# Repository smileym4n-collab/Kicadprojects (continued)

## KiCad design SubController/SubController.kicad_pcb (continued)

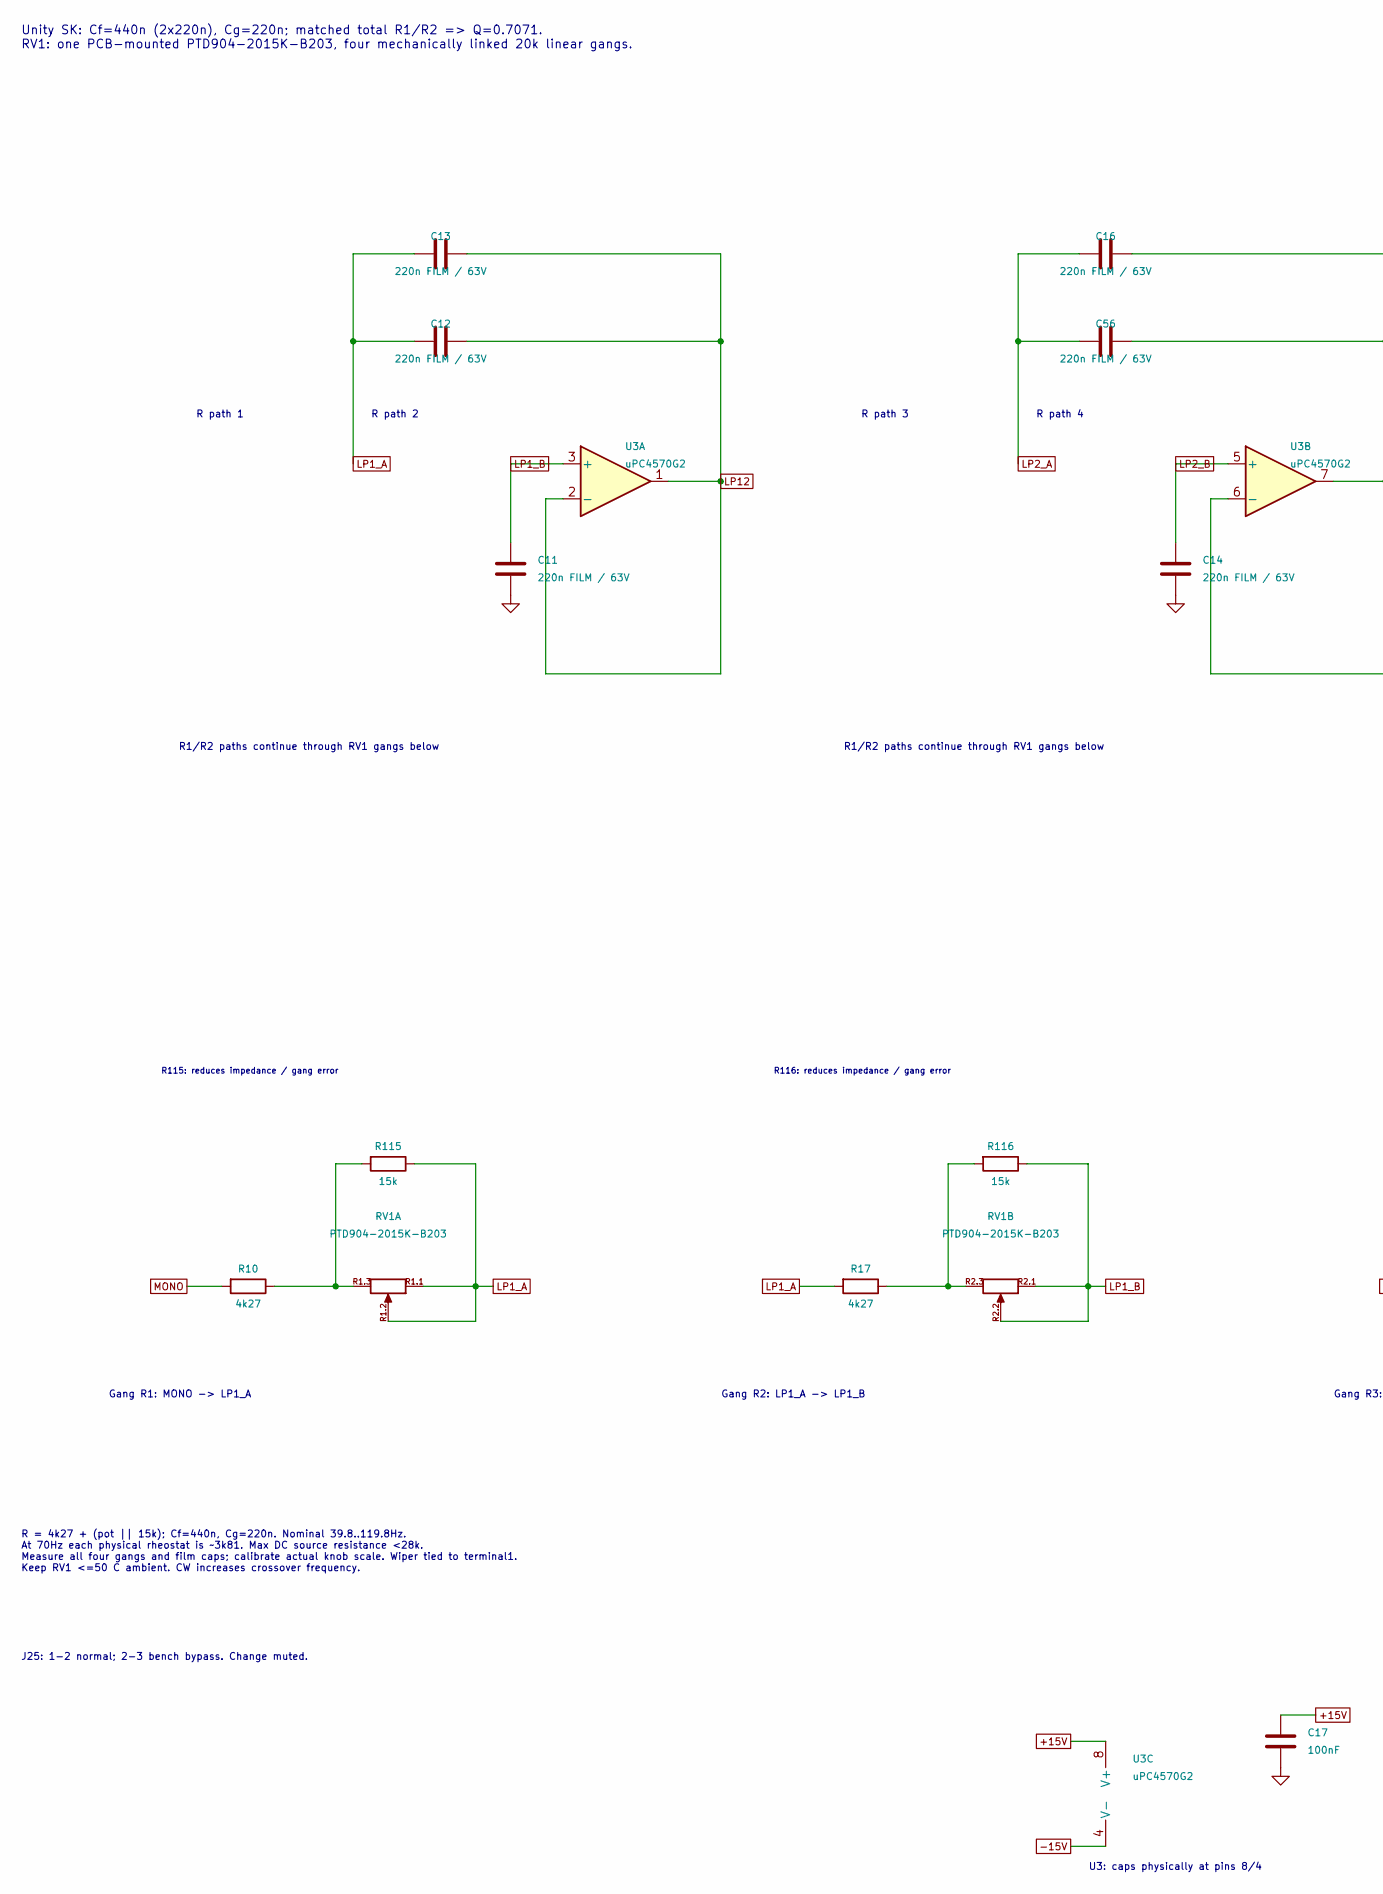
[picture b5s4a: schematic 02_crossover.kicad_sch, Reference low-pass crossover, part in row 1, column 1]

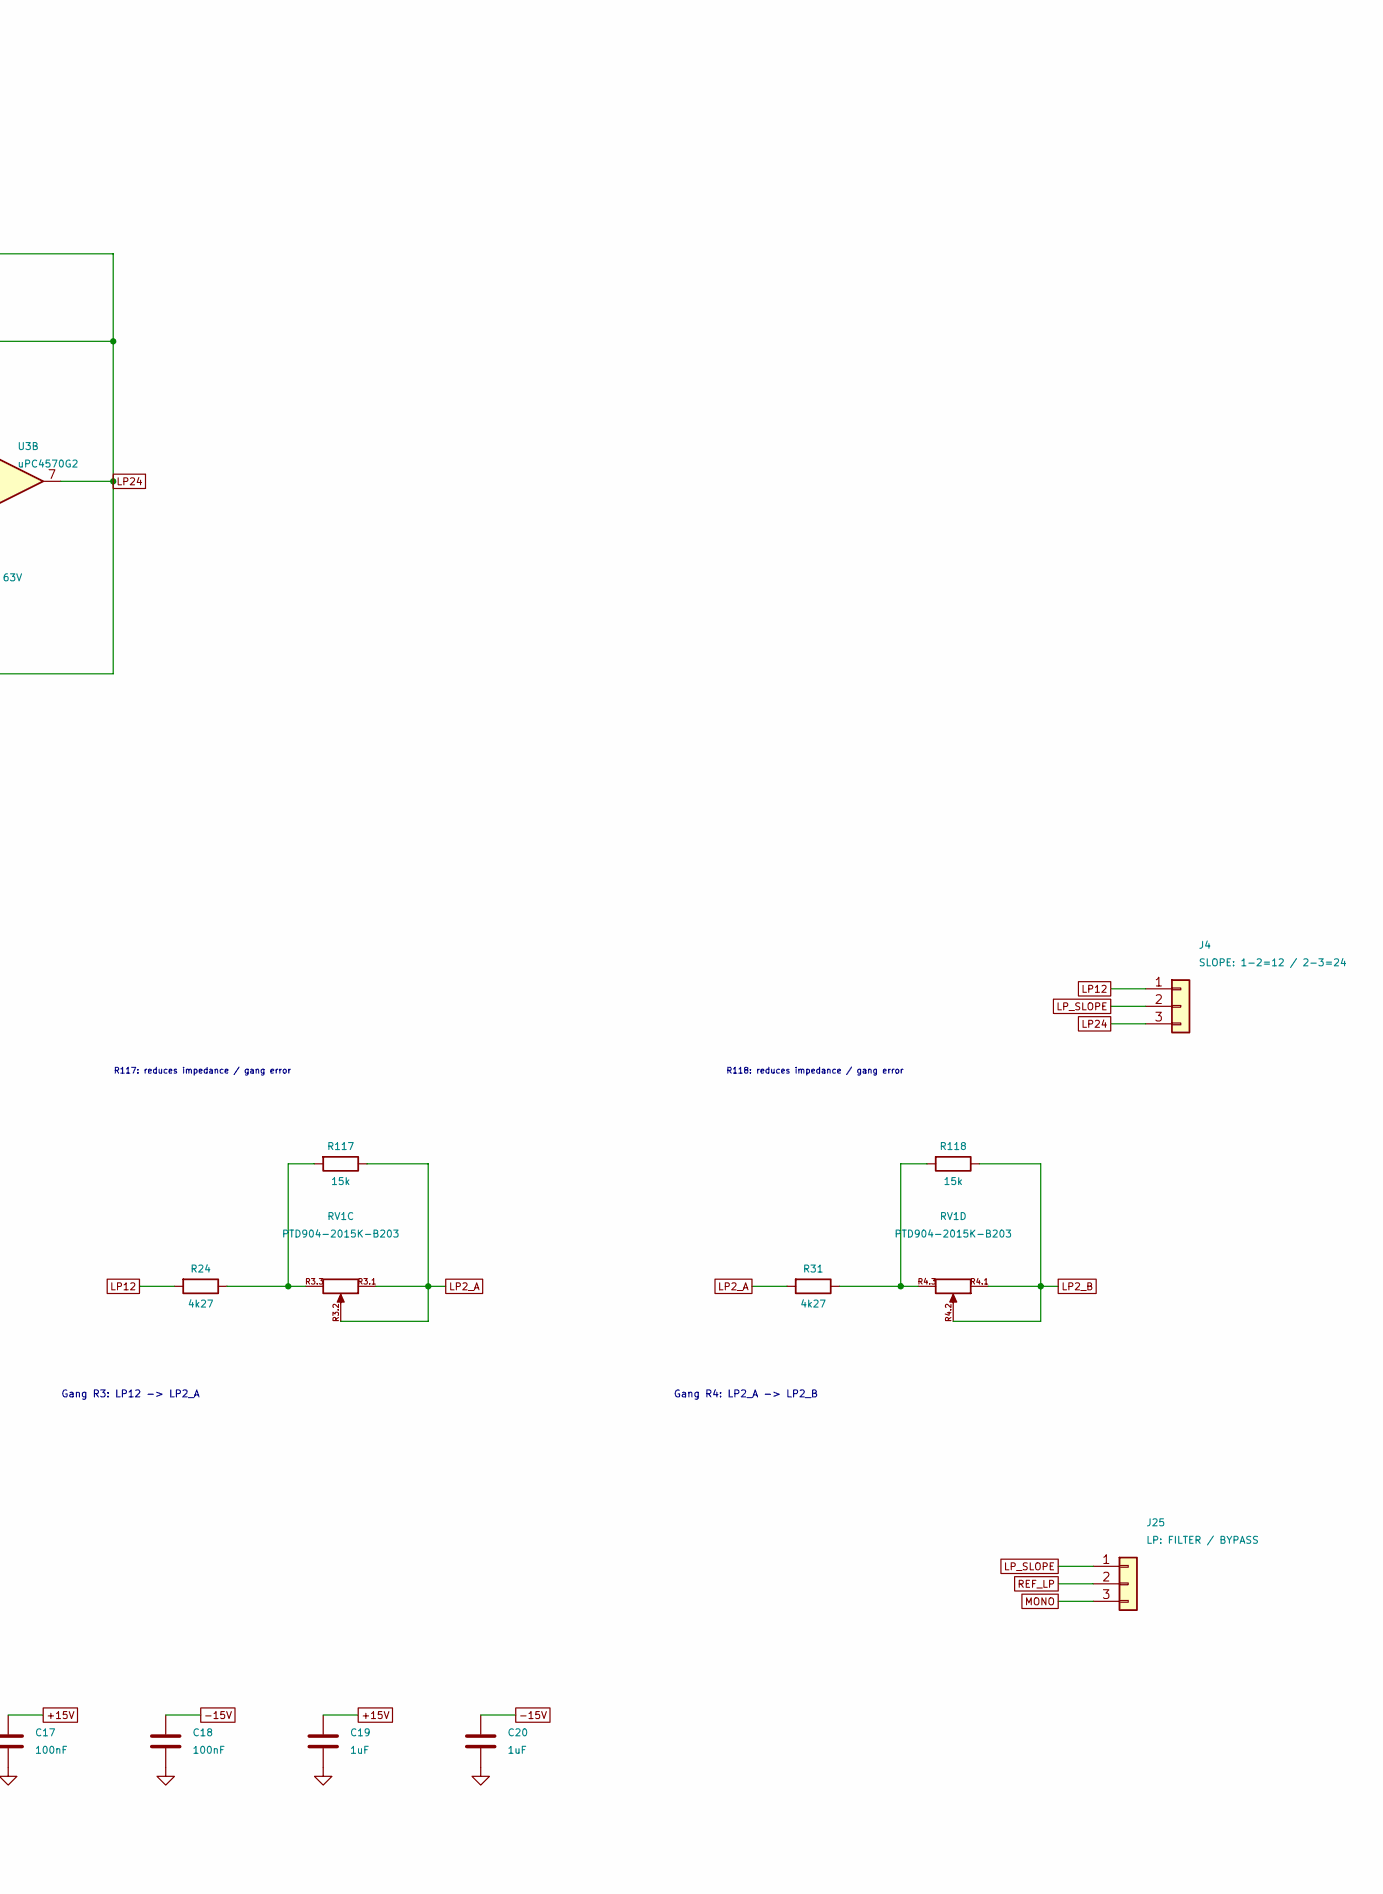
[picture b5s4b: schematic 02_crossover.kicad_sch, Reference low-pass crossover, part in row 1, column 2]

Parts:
C11, C12, C13, C14, C16, C56: 220n FILM / 63V; C_Rect_L7.2mm_W2.5mm_P5.00mm_FKS2_FKP2_MKS2_MKP2
C17, C18: 100nF; C_1206_3216Metric
C19, C20: 1uF; C_1206_3216Metric
J4: SLOPE: 1-2=12 / 2-3=24; PinHeader_1x03_P2.54mm_Vertical
J25: LP: FILTER / BYPASS; PinHeader_1x03_P2.54mm_Vertical
R10, R17, R24, R31: 4k27; R_0805_2012Metric
R115, R116, R117, R118: 15k; R_0805_2012Metric
RV1: PTD904-2015K-B203; PTD904_2015K_B203_Horizontal
U3: uPC4570G2; SOP-8_uPC4570G2_4.4x5.2mm_P1.27mm

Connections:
+15V: C17.1, C19.1, U3.8 (V+); also elsewhere on the board
-15V: C18.1, C20.1, U3.4 (V-); also elsewhere on the board
GND: C11.2, C14.2, C17.2, C18.2, C19.2, C20.2; also elsewhere on the board
LP1_A: C12.2, C13.2, R17.2, R115.1, RV1.R1.1 (1), RV1.R1.2 (2)
LP1_B: C11.1, R116.1, RV1.R2.1 (1), RV1.R2.2 (2), U3.3 (+)
LP2_A: C16.2, C56.2, R31.2, R117.1, RV1.R3.1 (1), RV1.R3.2 (2)
LP2_B: C14.1, R118.1, RV1.R4.1 (1), RV1.R4.2 (2), U3.5 (+)
LP12: C12.1, C13.1, J4.1, R24.2, U3.1, U3.2 (-)
LP24: C16.1, C56.1, J4.3, U3.6 (-), U3.7
LP_SLOPE: J4.2, J25.1; also elsewhere on the board
MONO: J25.3, R10.2; also elsewhere on the board
unnamed: R10.1, R115.2, RV1.R1.3 (3)
unnamed: R17.1, R116.2, RV1.R2.3 (3)
unnamed: R24.1, R117.2, RV1.R3.3 (3)
unnamed: R31.1, R118.2, RV1.R4.3 (3)
REF_LP: J25.2; also elsewhere on the board

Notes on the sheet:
R1/R2 paths continue through RV1 gangs below
Gang R1: MONO -> LP1_A
U3: caps physically at pins 8/4
Unity SK: Cf=440n (2x220n), Cg=220n; matched total R1/R2 => Q=0.7071. RV1: one PCB-mounted PTD904-2015K-B203, four mechanically linked 20k linear gangs.
J25: 1-2 normal; 2-3 bench bypass. Change muted.
R path 2
Gang R3: LP12 -> LP2_A
R117: reduces impedance / gang error
R118: reduces impedance / gang error
R path 1
R115: reduces impedance / gang error
R path 3
Gang R2: LP1_A -> LP1_B
R path 4
R = 4k27 + (pot || 15k); Cf=440n, Cg=220n. Nominal 39.8..119.8Hz. At 70Hz each physical rheostat is ~3k81. Max DC source resistance <28k. Measure all four gangs and film caps; calibrate actual knob scale. Wiper tied to terminal1. Keep RV1 <=50 C ambient. CW increases crossover frequency.
Gang R4: LP2_A -> LP2_B
R116: reduces impedance / gang error

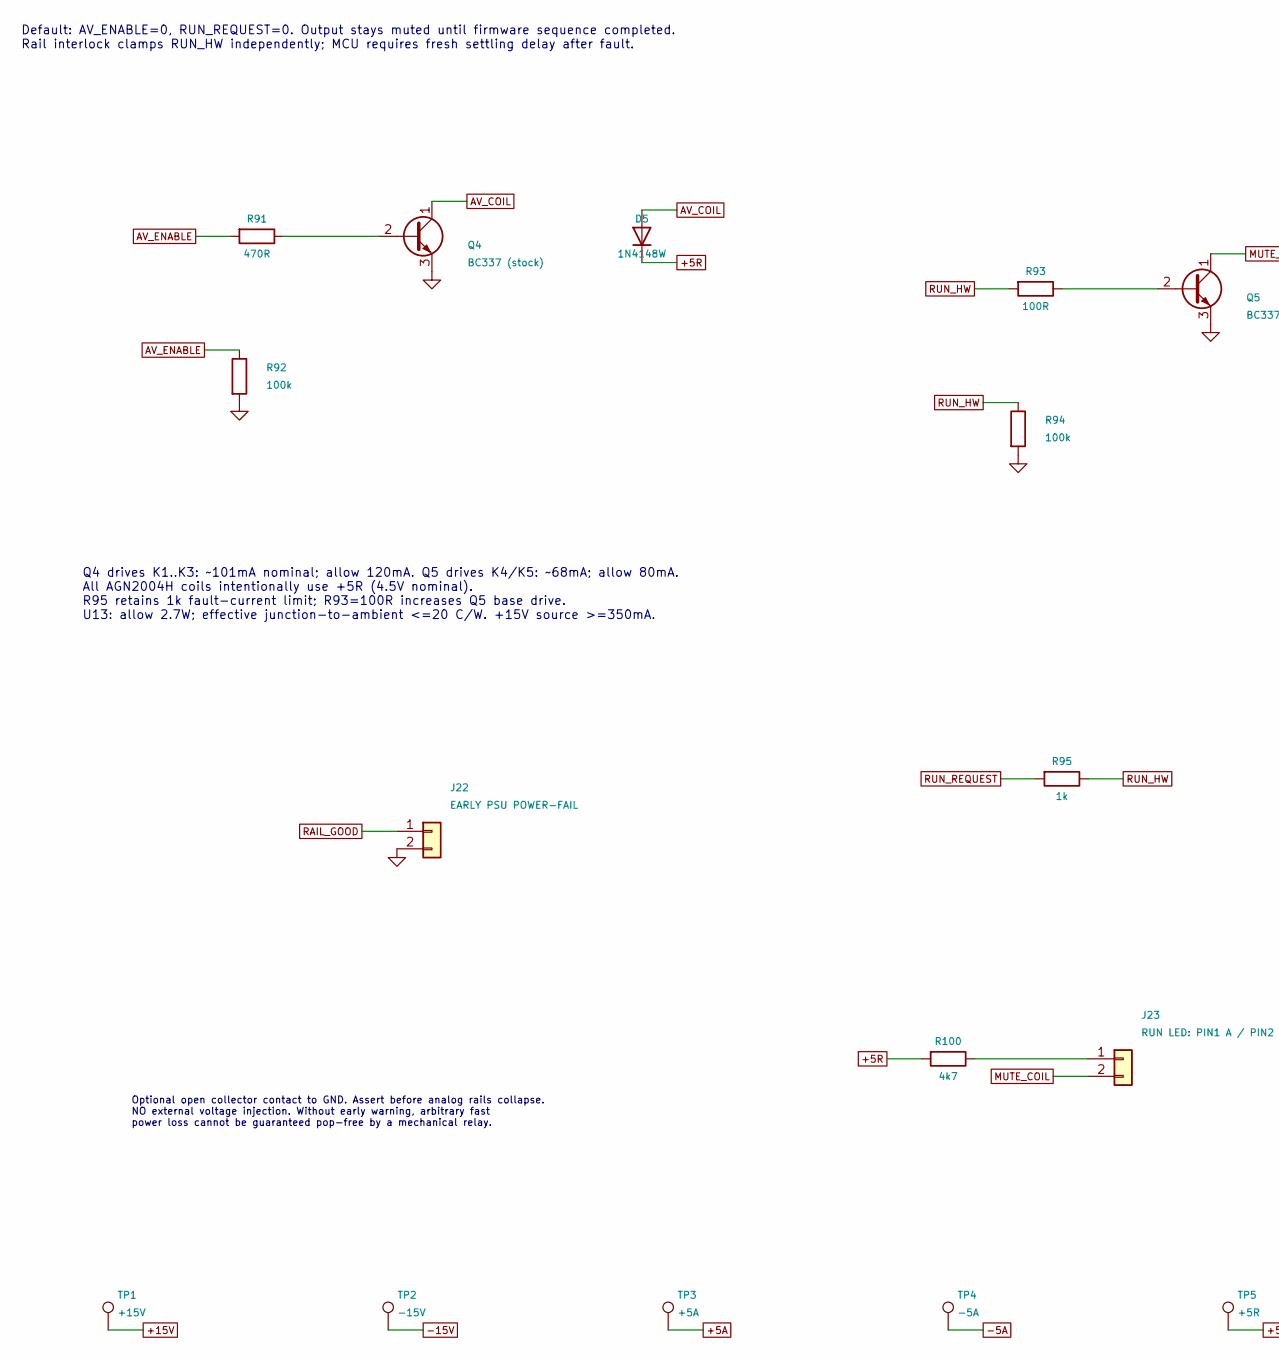
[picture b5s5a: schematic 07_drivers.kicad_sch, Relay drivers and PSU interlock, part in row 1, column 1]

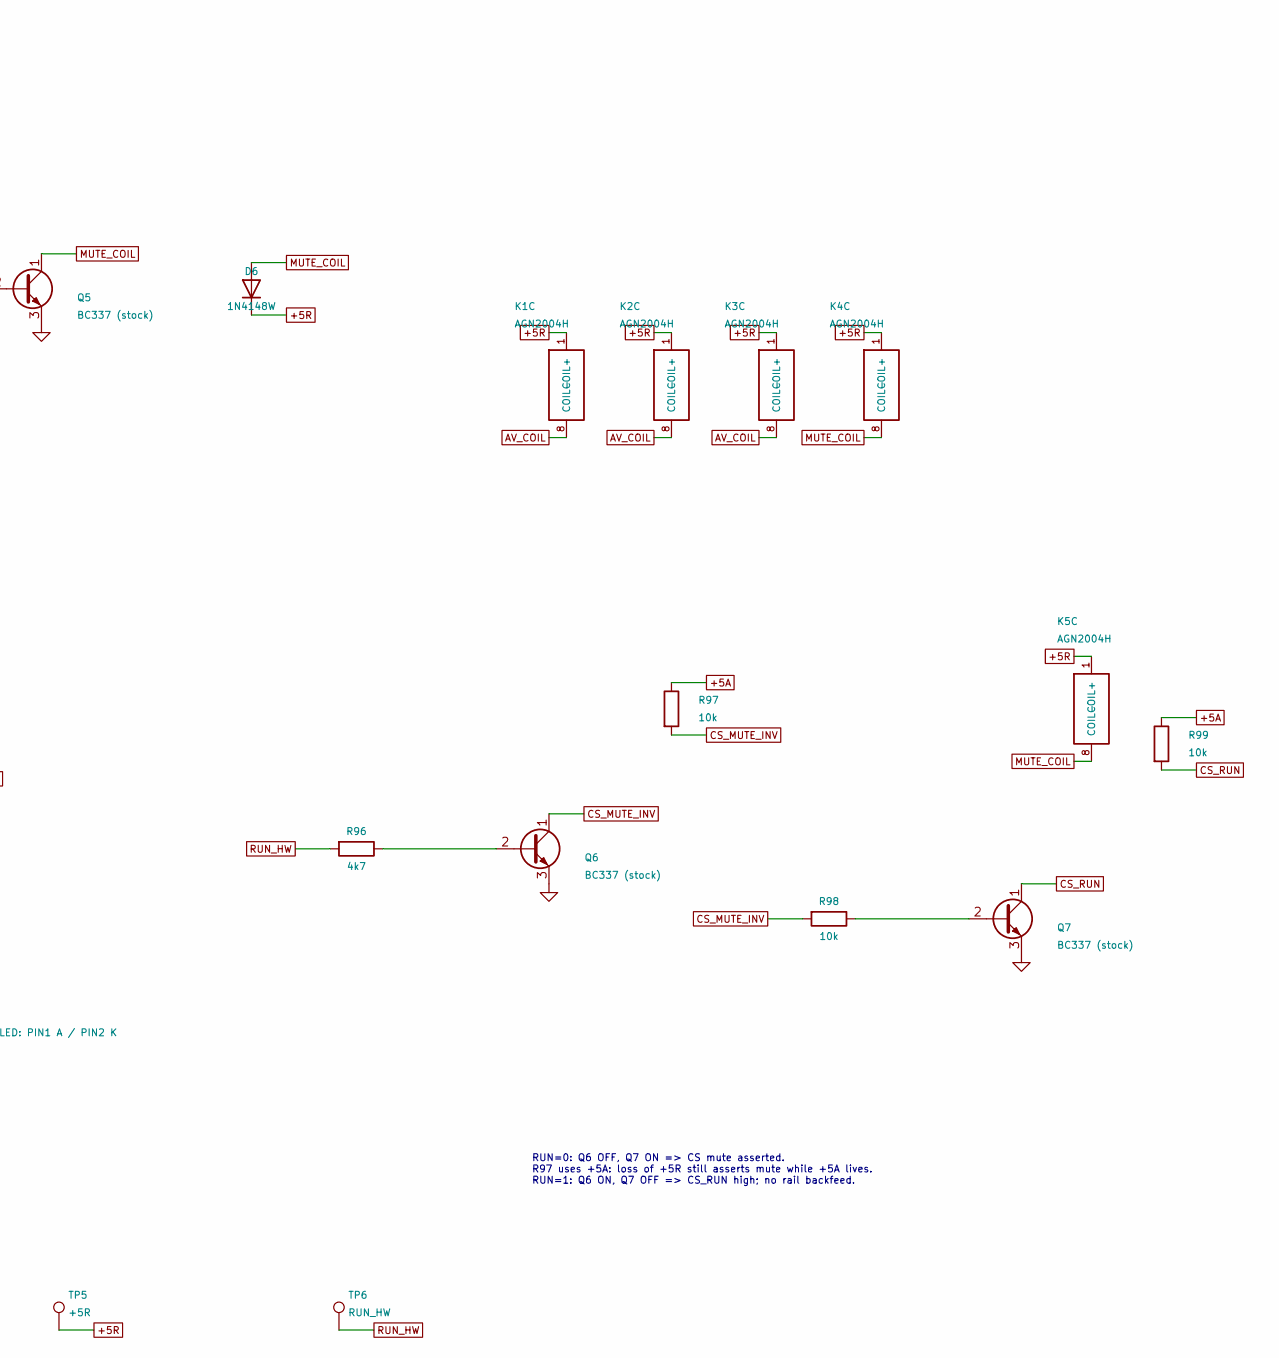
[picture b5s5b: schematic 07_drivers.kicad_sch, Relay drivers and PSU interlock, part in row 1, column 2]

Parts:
D5, D6: 1N4148W; D_SOD-123
J22: EARLY PSU POWER-FAIL; PinHeader_1x02_P2.54mm_Vertical
J23: RUN LED: PIN1 A / PIN2 K; PinHeader_1x02_P2.54mm_Vertical
K1, K2, K3, K4, K5: AGN2004H; Relay_DPDT_Panasonic_AGN2004H
Q4, Q5, Q6, Q7: BC337 (stock); TO-92_Inline
R91: 470R; R_0805_2012Metric
R92, R94: 100k; R_0805_2012Metric
R93: 100R; R_0805_2012Metric
R95: 1k; R_0805_2012Metric
R96, R100: 4k7; R_0805_2012Metric
R97, R98, R99: 10k; R_0805_2012Metric
TP1: +15V; TestPoint_Pad_D1.5mm
TP2: -15V; TestPoint_Pad_D1.5mm
TP3: +5A; TestPoint_Pad_D1.5mm
TP4: -5A; TestPoint_Pad_D1.5mm
TP5: +5R; TestPoint_Pad_D1.5mm
TP6: RUN_HW; TestPoint_Pad_D1.5mm

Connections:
+5A: R97.1, R99.1, TP3.1 (1_1); also elsewhere on the board
+5R: D5.1 (K), D6.1 (K), K1.1 (COIL+), K2.1 (COIL+), K3.1 (COIL+), K4.1 (COIL+), K5.1 (COIL+), R100.2, TP5.1 (1_1); also elsewhere on the board
+15V: TP1.1 (1_1); also elsewhere on the board
-5A: TP4.1 (1_1); also elsewhere on the board
-15V: TP2.1 (1_1); also elsewhere on the board
AV_COIL: D5.2 (A), K1.8 (COIL-), K2.8 (COIL-), K3.8 (COIL-), Q4.1 (C)
AV_ENABLE: R91.2, R92.1; also elsewhere on the board
CS_MUTE_INV: Q6.1 (C), R97.2, R98.2
CS_RUN: Q7.1 (C), R99.2; also elsewhere on the board
GND: J22.2, Q4.3 (E), Q5.3 (E), Q6.3 (E), Q7.3 (E), R92.2, R94.2; also elsewhere on the board
MUTE_COIL: D6.2 (A), J23.2, K4.8 (COIL-), K5.8 (COIL-), Q5.1 (C)
unnamed: J23.1, R100.1
unnamed: Q4.2 (B), R91.1
unnamed: Q5.2 (B), R93.1
unnamed: Q6.2 (B), R96.1
unnamed: Q7.2 (B), R98.1
RAIL_GOOD: J22.1; also elsewhere on the board
RUN_HW: R93.2, R94.1, R95.1, R96.2, TP6.1 (1_1); also elsewhere on the board
RUN_REQUEST: R95.2; also elsewhere on the board

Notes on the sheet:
Q4 drives K1..K3: ~101mA nominal; allow 120mA. Q5 drives K4/K5: ~68mA; allow 80mA. All AGN2004H coils intentionally use +5R (4.5V nominal). R95 retains 1k fault-current limit; R93=100R increases Q5 base drive. U13: allow 2.7W; effective junction-to-ambient <=20 C/W. +15V source >=350mA.
Default: AV_ENABLE=0, RUN_REQUEST=0. Output stays muted until firmware sequence completed. Rail interlock clamps RUN_HW independently; MCU requires fresh settling delay after fault.
Optional open collector contact to GND. Assert before analog rails collapse. NO external voltage injection. Without early warning, arbitrary fast power loss cannot be guaranteed pop-free by a mechanical relay.
RUN=0: Q6 OFF, Q7 ON => CS mute asserted. R97 uses +5A: loss of +5R still asserts mute while +5A lives. RUN=1: Q6 ON, Q7 OFF => CS_RUN high; no rail backfeed.

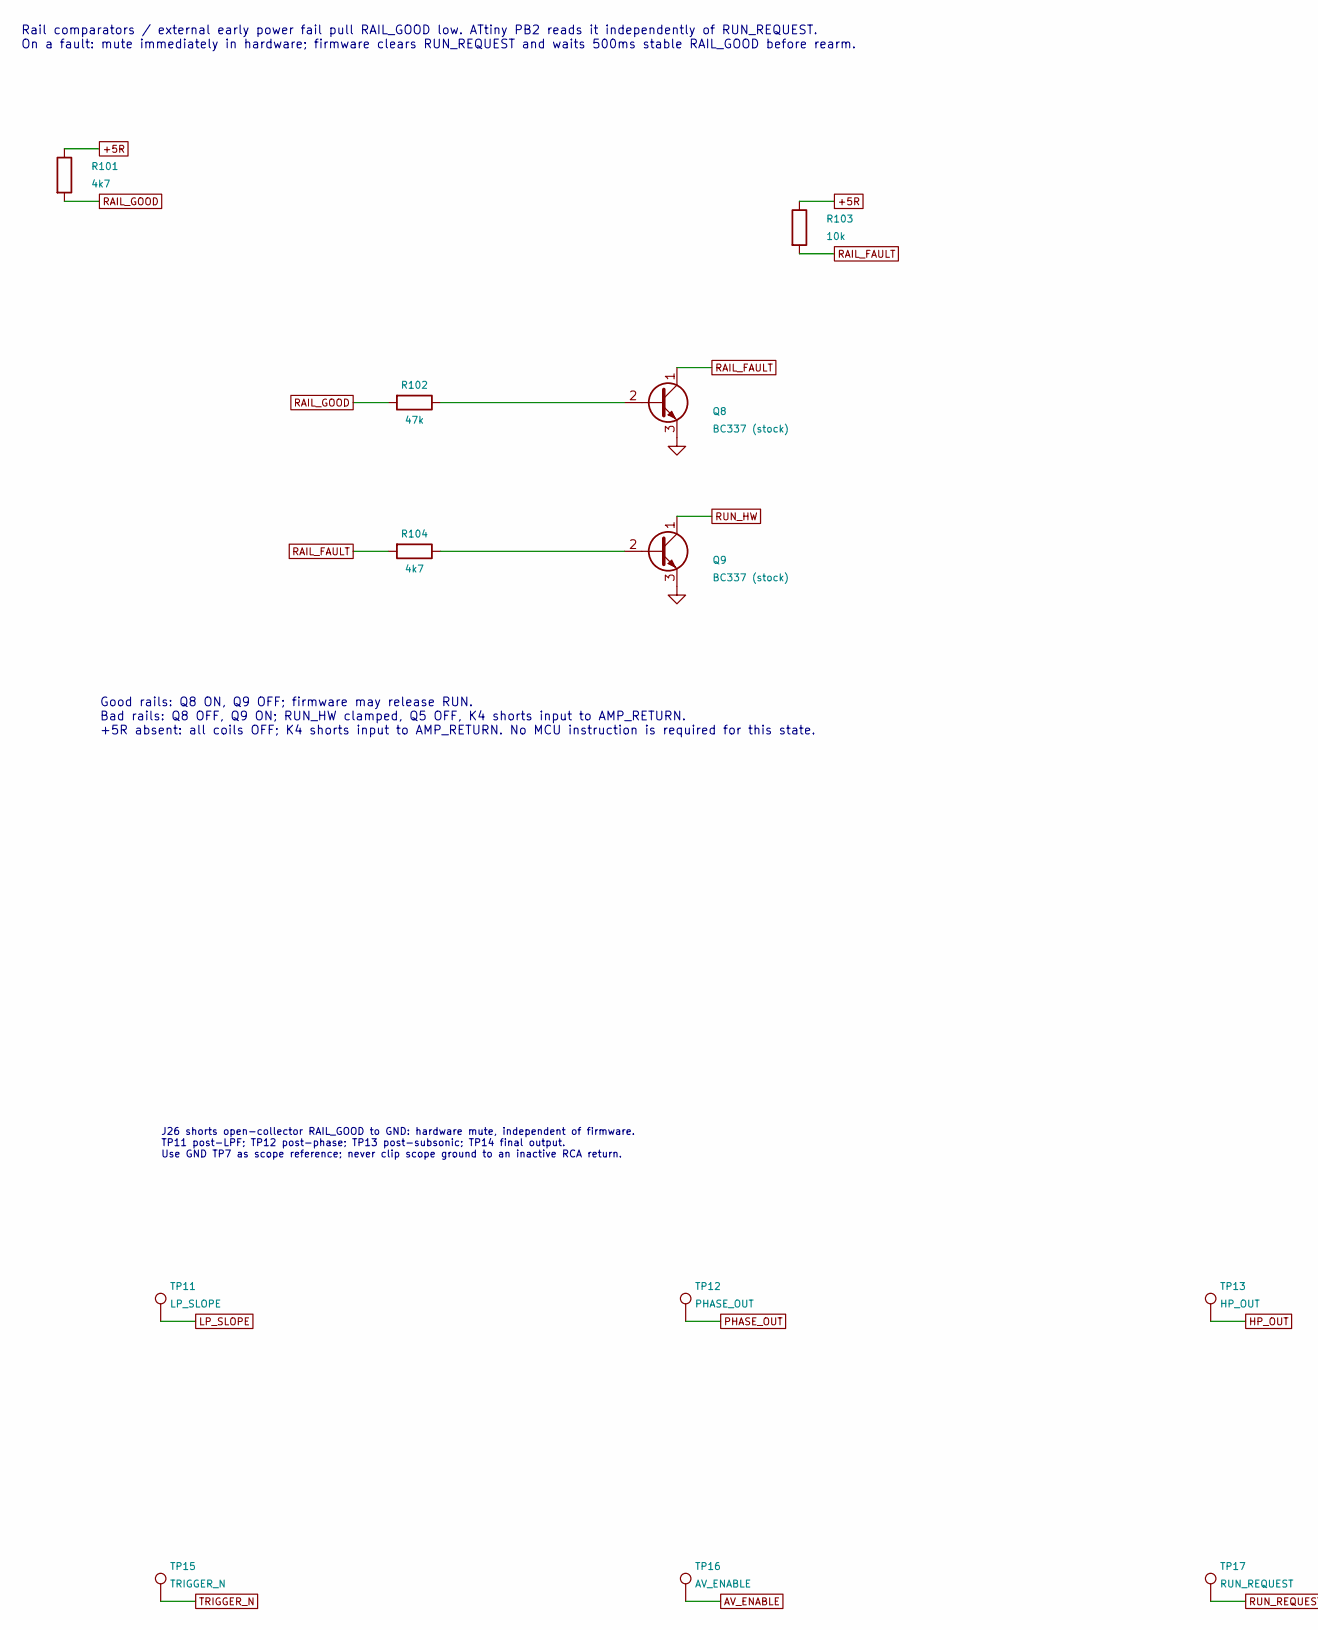
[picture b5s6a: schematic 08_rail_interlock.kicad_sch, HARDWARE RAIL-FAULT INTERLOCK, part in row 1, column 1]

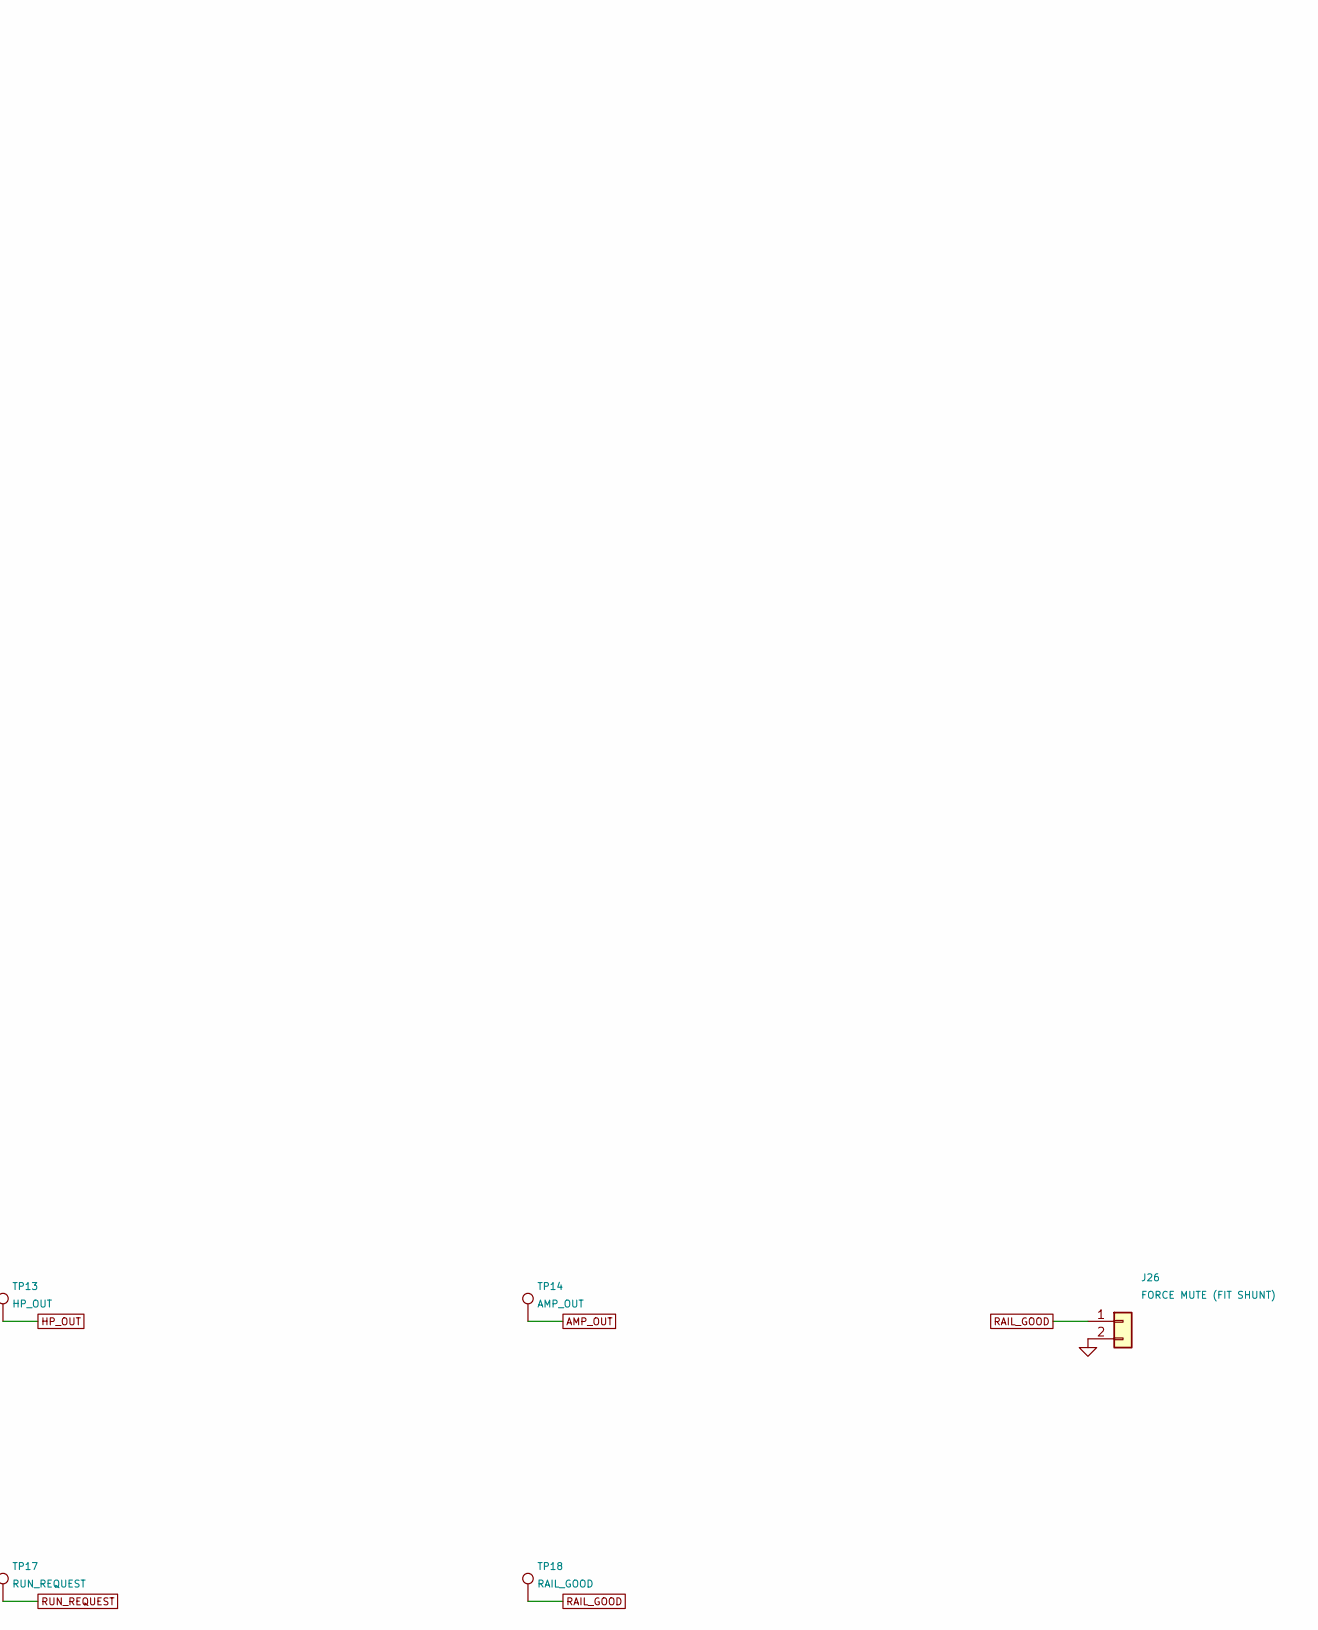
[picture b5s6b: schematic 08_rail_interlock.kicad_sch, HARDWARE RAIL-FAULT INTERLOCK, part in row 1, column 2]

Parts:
J26: FORCE MUTE (FIT SHUNT); PinHeader_1x02_P2.54mm_Vertical
Q8, Q9: BC337 (stock); TO-92_Inline
R101, R104: 4k7; R_0805_2012Metric
R102: 47k; R_0805_2012Metric
R103: 10k; R_0805_2012Metric
TP11: LP_SLOPE; TestPoint_Pad_D1.5mm
TP12: PHASE_OUT; TestPoint_Pad_D1.5mm
TP13: HP_OUT; TestPoint_Pad_D1.5mm
TP14: AMP_OUT; TestPoint_Pad_D1.5mm
TP15: TRIGGER_N; TestPoint_Pad_D1.5mm
TP16: AV_ENABLE; TestPoint_Pad_D1.5mm
TP17: RUN_REQUEST; TestPoint_Pad_D1.5mm
TP18: RAIL_GOOD; TestPoint_Pad_D1.5mm

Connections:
+5R: R101.1, R103.1; also elsewhere on the board
AMP_OUT: TP14.1 (1_1); also elsewhere on the board
AV_ENABLE: TP16.1 (1_1); also elsewhere on the board
GND: J26.2, Q8.3 (E), Q9.3 (E); also elsewhere on the board
HP_OUT: TP13.1 (1_1); also elsewhere on the board
LP_SLOPE: TP11.1 (1_1); also elsewhere on the board
unnamed: Q8.2 (B), R102.1
unnamed: Q9.2 (B), R104.1
PHASE_OUT: TP12.1 (1_1); also elsewhere on the board
RAIL_FAULT: Q8.1 (C), R103.2, R104.2
RAIL_GOOD: J26.1, R101.2, R102.2, TP18.1 (1_1); also elsewhere on the board
RUN_HW: Q9.1 (C); also elsewhere on the board
RUN_REQUEST: TP17.1 (1_1); also elsewhere on the board
TRIGGER_N: TP15.1 (1_1); also elsewhere on the board

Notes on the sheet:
J26 shorts open-collector RAIL_GOOD to GND: hardware mute, independent of firmware. TP11 post-LPF; TP12 post-phase; TP13 post-subsonic; TP14 final output. Use GND TP7 as scope reference; never clip scope ground to an inactive RCA return.
Rail comparators / external early power fail pull RAIL_GOOD low. ATtiny PB2 reads it independently of RUN_REQUEST. On a fault: mute immediately in hardware; firmware clears RUN_REQUEST and waits 500ms stable RAIL_GOOD before rearm.
Good rails: Q8 ON, Q9 OFF; firmware may release RUN. Bad rails: Q8 OFF, Q9 ON; RUN_HW clamped, Q5 OFF, K4 shorts input to AMP_RETURN. +5R absent: all coils OFF; K4 shorts input to AMP_RETURN. No MCU instruction is required for this state.
